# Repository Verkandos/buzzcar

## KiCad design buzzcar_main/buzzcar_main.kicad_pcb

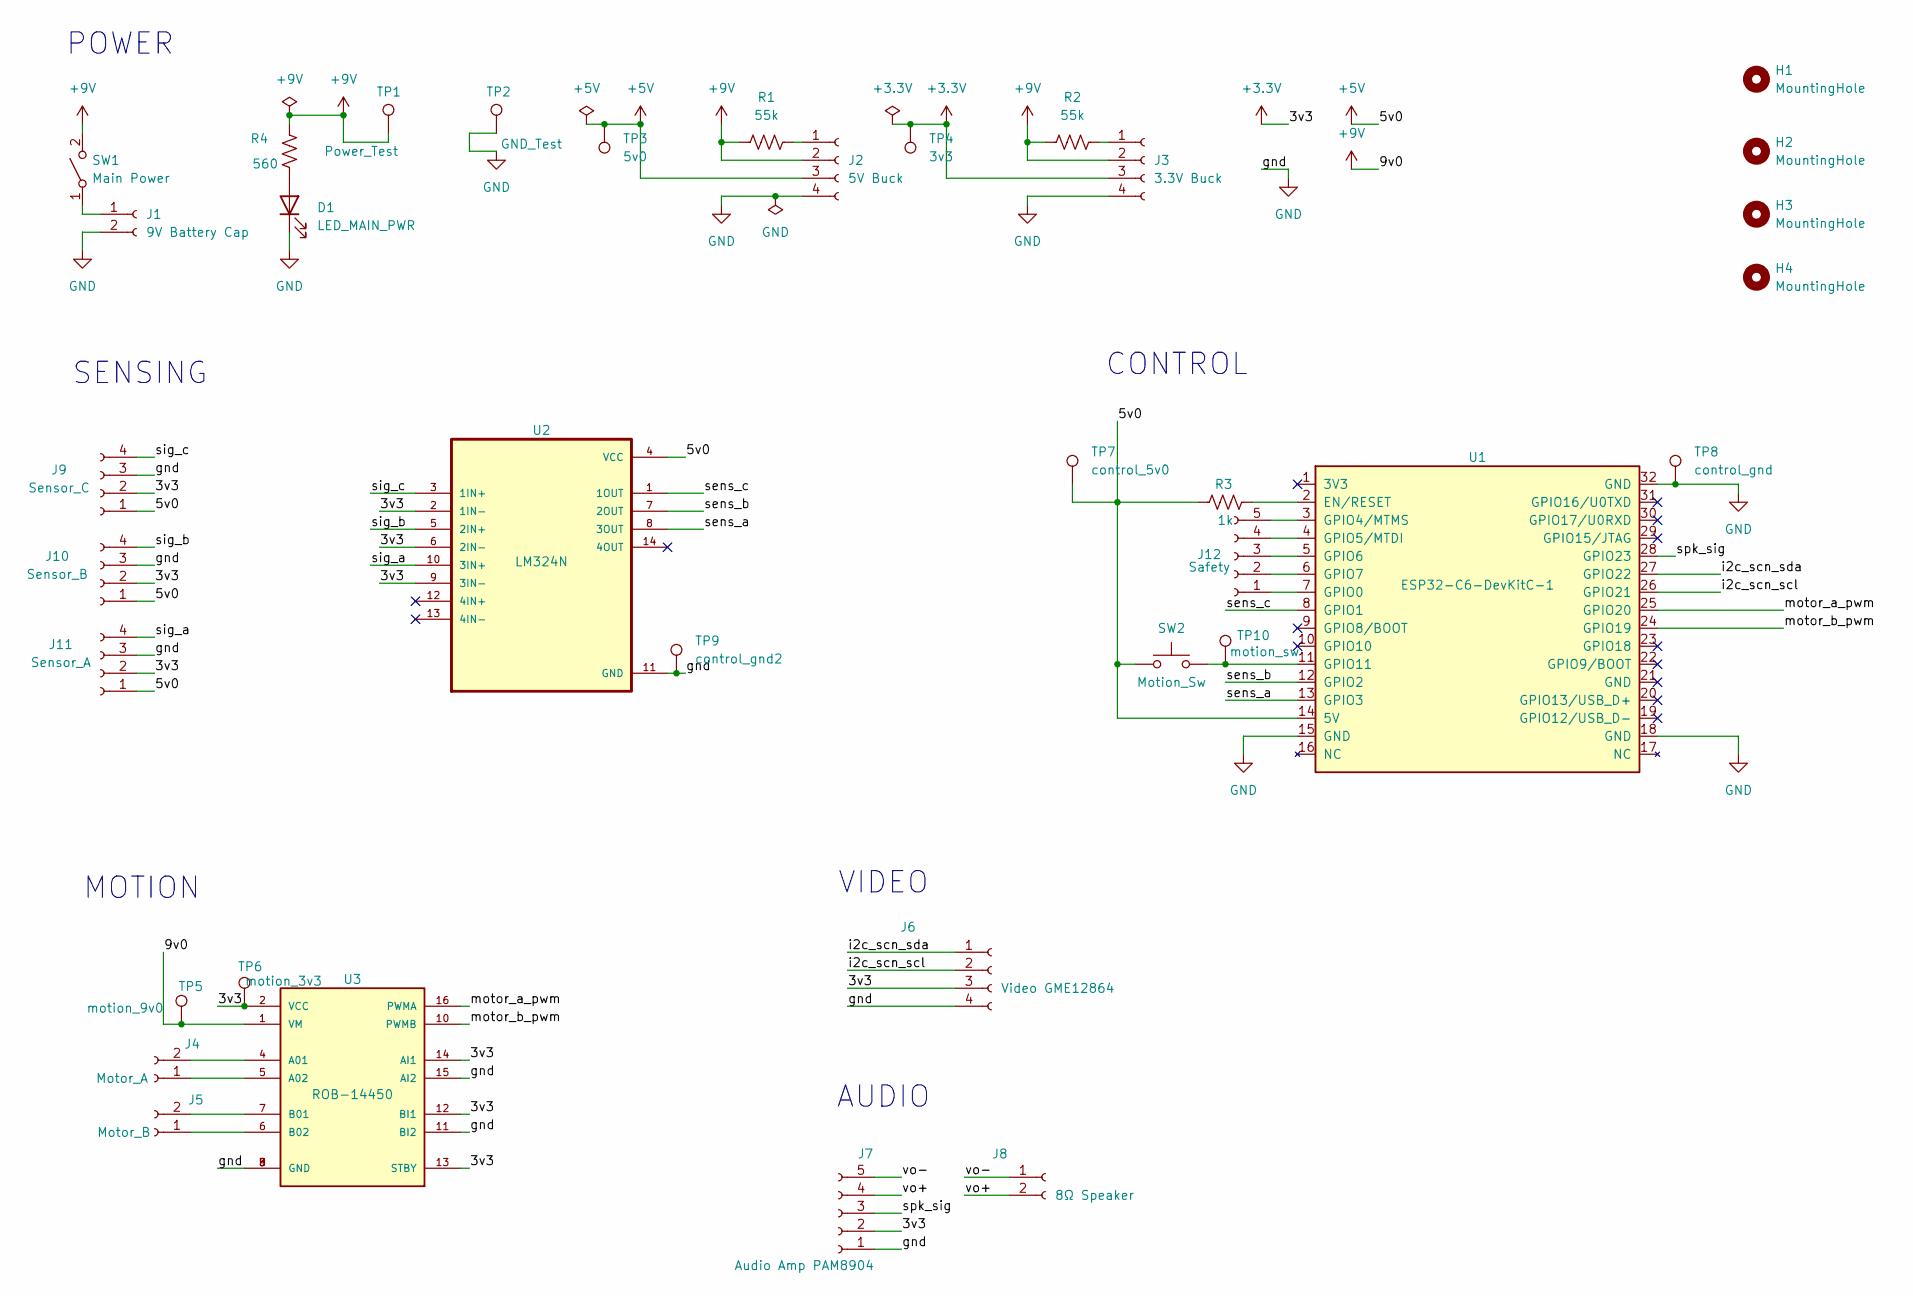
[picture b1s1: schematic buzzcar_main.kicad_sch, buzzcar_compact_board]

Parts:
D1: LED_MAIN_PWR; LED_D3.0mm
H1, H2, H3, H4: MountingHole; MountingHole_3mm
J1: 9V Battery Cap; PinHeader_1x02_P2.54mm_Vertical
J2: 5V Buck; PinHeader_1x04_P2.54mm_Vertical
J3: 3.3V Buck; PinHeader_1x04_P2.54mm_Vertical
J4: Motor_A; PinHeader_1x02_P2.54mm_Vertical
J5: Motor_B; PinHeader_1x02_P2.54mm_Vertical
J6: Video GME12864; PinHeader_1x04_P2.54mm_Vertical
J7: Audio Amp PAM8904; PinHeader_1x05_P2.54mm_Vertical
J8: 8Ω Speaker; PinHeader_1x02_P2.54mm_Vertical
J9: Sensor_C; PinHeader_1x04_P2.54mm_Vertical
J10: Sensor_B; PinHeader_1x04_P2.54mm_Vertical
J11: Sensor_A; PinHeader_1x04_P2.54mm_Vertical
J12: Safety; PinHeader_1x05_P2.54mm_Vertical
R1, R2: 55k; R_Axial_DIN0207_L6.3mm_D2.5mm_P10.16mm_Horizontal
R3: 1k; R_Axial_DIN0207_L6.3mm_D2.5mm_P10.16mm_Horizontal
R4: 560; R_Axial_DIN0207_L6.3mm_D2.5mm_P10.16mm_Horizontal
SW1: Main Power; PinHeader_1x02_P2.54mm_Vertical
SW2: Motion_Sw; PinHeader_1x02_P2.54mm_Vertical
TP1: Power_Test; TestPoint_Loop_D2.60mm_Drill1.6mm_Beaded
TP2: GND_Test; TestPoint_Loop_D2.60mm_Drill1.6mm_Beaded
TP3: 5v0; TestPoint_Loop_D2.60mm_Drill1.6mm_Beaded
TP4: 3v3; TestPoint_Loop_D2.60mm_Drill1.6mm_Beaded
TP5: motion_9v0; TestPoint_Loop_D2.60mm_Drill1.6mm_Beaded
TP6: motion_3v3; TestPoint_Loop_D2.60mm_Drill1.6mm_Beaded
TP7: control_5v0; TestPoint_Loop_D2.60mm_Drill1.6mm_Beaded
TP8: control_gnd; TestPoint_Loop_D2.60mm_Drill1.6mm_Beaded
TP9: control_gnd2; TestPoint_Loop_D2.60mm_Drill1.6mm_Beaded
TP10: motion_sw; TestPoint_Loop_D2.60mm_Drill1.6mm_Beaded
U1: ESP32-C6-DevKitC-1
U2: LM324N; DIP794W45P254L1969H508Q14
U3: ROB-14450; MODULE_ROB-14450; PARTREV 11-13-17

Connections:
+3.3V: J3.3, J6.3, J7.2, J9.2, J10.2, J11.2, TP4.1, TP6.1, U2.2 (1IN-), U2.6 (2IN-), U2.9 (3IN-), U3.2 (VCC), U3.12 (BI1), U3.13 (STBY), U3.14 (AI1)
+5V: J2.3, J9.1, J10.1, J11.1, R3.1, SW2.1, TP3.1, TP7.1, U1.14 (5V), U2.4 (VCC)
+9V: J2.2, J3.2, R1.1, R2.1, R4.1, SW1.2 (B), TP1.1, TP5.1, U3.1 (VM)
/i2c_scn_scl: J6.2, U1.26 (GPIO21)
/i2c_scn_sda: J6.1, U1.27 (GPIO22)
/motor_a_pwm: U1.25 (GPIO20), U3.16 (PWMA)
/motor_b_pwm: U1.24 (GPIO19), U3.10 (PWMB)
/sens_a: U1.13 (GPIO3), U2.8 (3OUT)
/sens_b: U1.12 (GPIO2), U2.7 (2OUT)
/sens_c: U1.8 (GPIO1), U2.1 (1OUT)
/sig_a: J11.4, U2.10 (3IN+)
/sig_b: J10.4, U2.5 (2IN+)
/sig_c: J9.4, U2.3 (1IN+)
/spk_sig: J7.3, U1.28 (GPIO23)
/vo+: J7.4, J8.2
/vo-: J7.5, J8.1
GND: D1.1 (K), J1.2, J2.4, J3.4, J6.4, J7.1, J9.3, J10.3, J11.3, TP2.1, TP8.1, TP9.1, U1.15 (GND), U1.18 (GND), U1.32 (GND), U2.11 (GND), U3.3 (GND), U3.8 (GND), U3.9 (GND), U3.11 (BI2), U3.15 (AI2)
unnamed: D1.2 (A), R4.2
unnamed: J1.1, SW1.1 (A)
unnamed: J2.1, R1.2
unnamed: J3.1, R2.2
unnamed: J4.1, U3.5 (A02)
unnamed: J4.2, U3.4 (A01)
unnamed: J5.1, U3.6 (B02)
unnamed: J5.2, U3.7 (B01)
unnamed: J12.1, U1.7 (GPIO0)
unnamed: J12.2, U1.6 (GPIO7)
unnamed: J12.3, U1.5 (GPIO6)
unnamed: J12.4, U1.4 (GPIO5/MTDI)
unnamed: J12.5, U1.3 (GPIO4/MTMS)
unnamed: R3.2, U1.2 (EN/RESET)
unnamed: SW2.2, TP10.1, U1.11 (GPIO11)

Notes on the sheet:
SENSING
VIDEO
POWER
CONTROL
AUDIO
MOTION

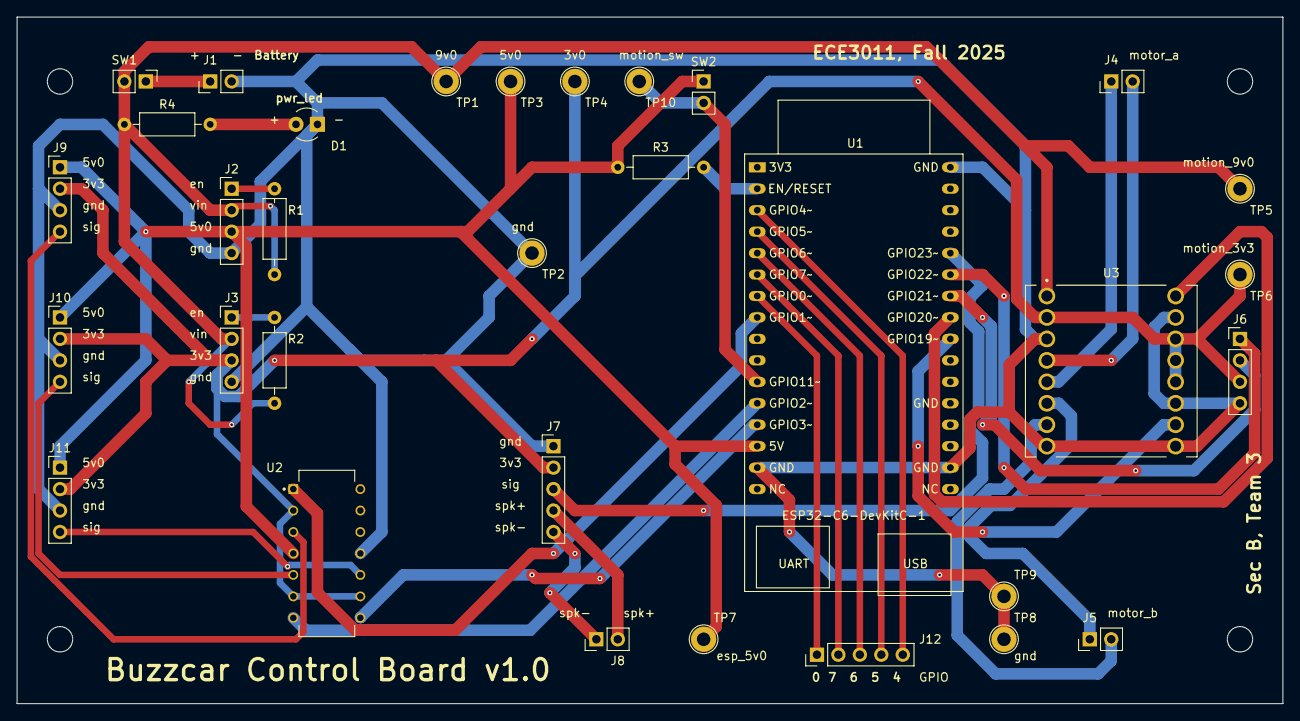
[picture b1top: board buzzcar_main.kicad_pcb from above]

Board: 2 copper layers, 149.9 x 81.3 mm, 36 parts (0 on the bottom side), 32 nets.

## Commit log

2025-09-05 Added PowerSubsystem.drawio
2025-09-05 Added SystemTopLevel.drawio
2025-09-05 Completed
2025-09-05 completePower.drawio
2025-09-05 oopsie.drawio
2025-09-05 final.drawio
2025-09-05 change_orientation
2025-09-05 move table
2025-09-05 final_top
2025-09-05 AwesomeDiagram
2025-09-14 Create file structure
2025-09-14 Create headers and main
2025-09-15 Initialized PlatformIO, create headers
2025-09-15 Implemented framework with TODO placeholders
2025-09-16 Implemented GPIOManager and FSM
2025-09-16 Updated GPIO Mapping
2025-09-16 Implemented Photosensor and Motor logic
2025-09-16 Created basic hardware integration testing
2025-09-18 Electrical Board Schematic v0.1
2025-09-18 added leds, mounting and test pins to schematic
2025-09-18 broke apart sensor subsystem to for two boards, to add connector pins
2025-09-19 PCB Layout v0.1 done
2025-09-19 Finalized Pin mapping
2025-09-19 Added LineDetector header and class
2025-09-19 Implemented PIDController class
2025-09-19 Fixed PhotoSensor bug
2025-09-19 PCB Layout v0.2 done - silkscreen errors left
2025-09-20 PCB v0.3 ready - fixed PCB traces, fixed crossing over into margins of drill holes
2025-09-21 Added silkscreen annotations, reduced board size to within 15cm x 15cm
2025-09-21 Buzzcar Control Board v1.0 complete
2025-09-21 v1.1 resolved initial DFM issues
2025-09-21 Final changes
2025-09-23 Implemented Forward State
2025-09-23 Implemented User Interface
2025-09-23 Implemented Idle State
2025-09-23 Implemented Stop State
2025-09-23 Updated IdleState to include ControlSubsystem class
2025-09-23 Implemented Turning (left and right) States
2025-09-24 Implemented PWM fix
2025-09-24 PWM testing demo
2025-09-24 Implemented PWM signal testing demo environment
2025-09-24 Implemented Event
2025-09-24 Implemented FSM
2025-09-26 Fixed Compile errors by removing circular dependencies
2025-09-26 Implemented logic for main ControlSubsystem to generate events
2025-09-26 Completed hardware initialization
2025-09-26 Added ControlSubsystem cleanup
2025-09-26 Implemented main
2025-09-26 Updated settings
2025-09-26 Serial Monitor fixed and implemented integration test
2025-09-30 Added comments to GPIOManager
2025-09-30 Added comments to FSM
2025-10-03 Added hardware integration with Speaker and Screen
2025-10-03 Software of Screen and Audio integrated with main control
2025-10-03 Created global variables to allow easier tuning
2025-10-03 Created System Integration tests
2025-10-03 Debugged Integration
2025-10-10 Updated System Integration tests and patched known bug
2025-10-17 Update Screen.cpp
    Updated visuals for the screen
2025-10-17 Update Speaker.cpp
    Updated speaker tones for when the airplane car is going different directions.
2025-10-17 Added multisampling to sensor readings
2025-10-17 Updated line position calculator
2025-10-17 Updated black & white thresholds
2025-10-17 Updated ForwardState to detect sharp turns to provide feedback
2025-10-17 Revert "Merge branch 'control_subsystem' of https://github.com/Verkandos/buzzcar into control_subsystem"
    This reverts commit e9d0c208b6ee1703a568eeeb507325a5d1940ac2, reversing
    changes made to 3c74616873775cc9f327bd6a32534b231ad36bae.
2025-10-17 Restoring files
2025-10-17 Fixed LineDetector
2025-10-17 Updated Integration Tests
2025-10-24 Moved GPIO Pin Definitions to ControlConfig.hpp
2025-10-24 Moved GPIO pins to ControlConfig.hpp
2025-10-24 Removed Pin defines and updated code to use ControlConfig.hpp
2025-10-24 Corrected logic for Line Detection
2025-10-24 Added ControlConfig settings
2025-10-24 Updated to delay to initialization of motors
2025-10-24 Added duty constrain
2025-10-24 Updated to include ControlConfig pin settings
2025-10-24 Added alternative pin mapping and potential fixes for integration issues
2025-10-24 Created dedicated motors and speaker integration tests
2025-10-24 Added build for Integration Fixes
2025-10-31 Updated UI/Button logic to reflect hardware change
2025-10-31 Added Wait for Serial Connection
2025-10-31 Updated pin comments
2025-10-31 Added edge case
2025-10-31 Added pin alternatives
2025-10-31 Updated platformio.ini
2025-11-03 Configured Pin 23 as High Impedance
2025-11-03 Added Pin 23 as high impedance
2025-11-03 Created fallback (no PID) based on integration test 9
2025-11-03 Added fallback environment
2025-11-03 Added Stop in Main
2025-11-03 Configured pin 23 as high impedance in hardware demo
2025-11-06 Inverted logic to match hardware
2025-11-06 Swapped Motor pins to match hardware
2025-11-06 Inverted logic for sensors to match hardware
2025-11-06 Added LastTurn variable and logic
2025-11-06 Corrected transitions
2025-11-06 Removed debug for cleaner serial monitor for debugging
2025-11-06 Updated turn logic to add LastTurn implementation
2025-11-06 Removed duplicate event handling
2025-11-07 Fixed FSM logic with Forward transitions
2025-11-09 Removed unused code
2025-11-09 Demo changes
2025-11-09 Removed outdated docs
